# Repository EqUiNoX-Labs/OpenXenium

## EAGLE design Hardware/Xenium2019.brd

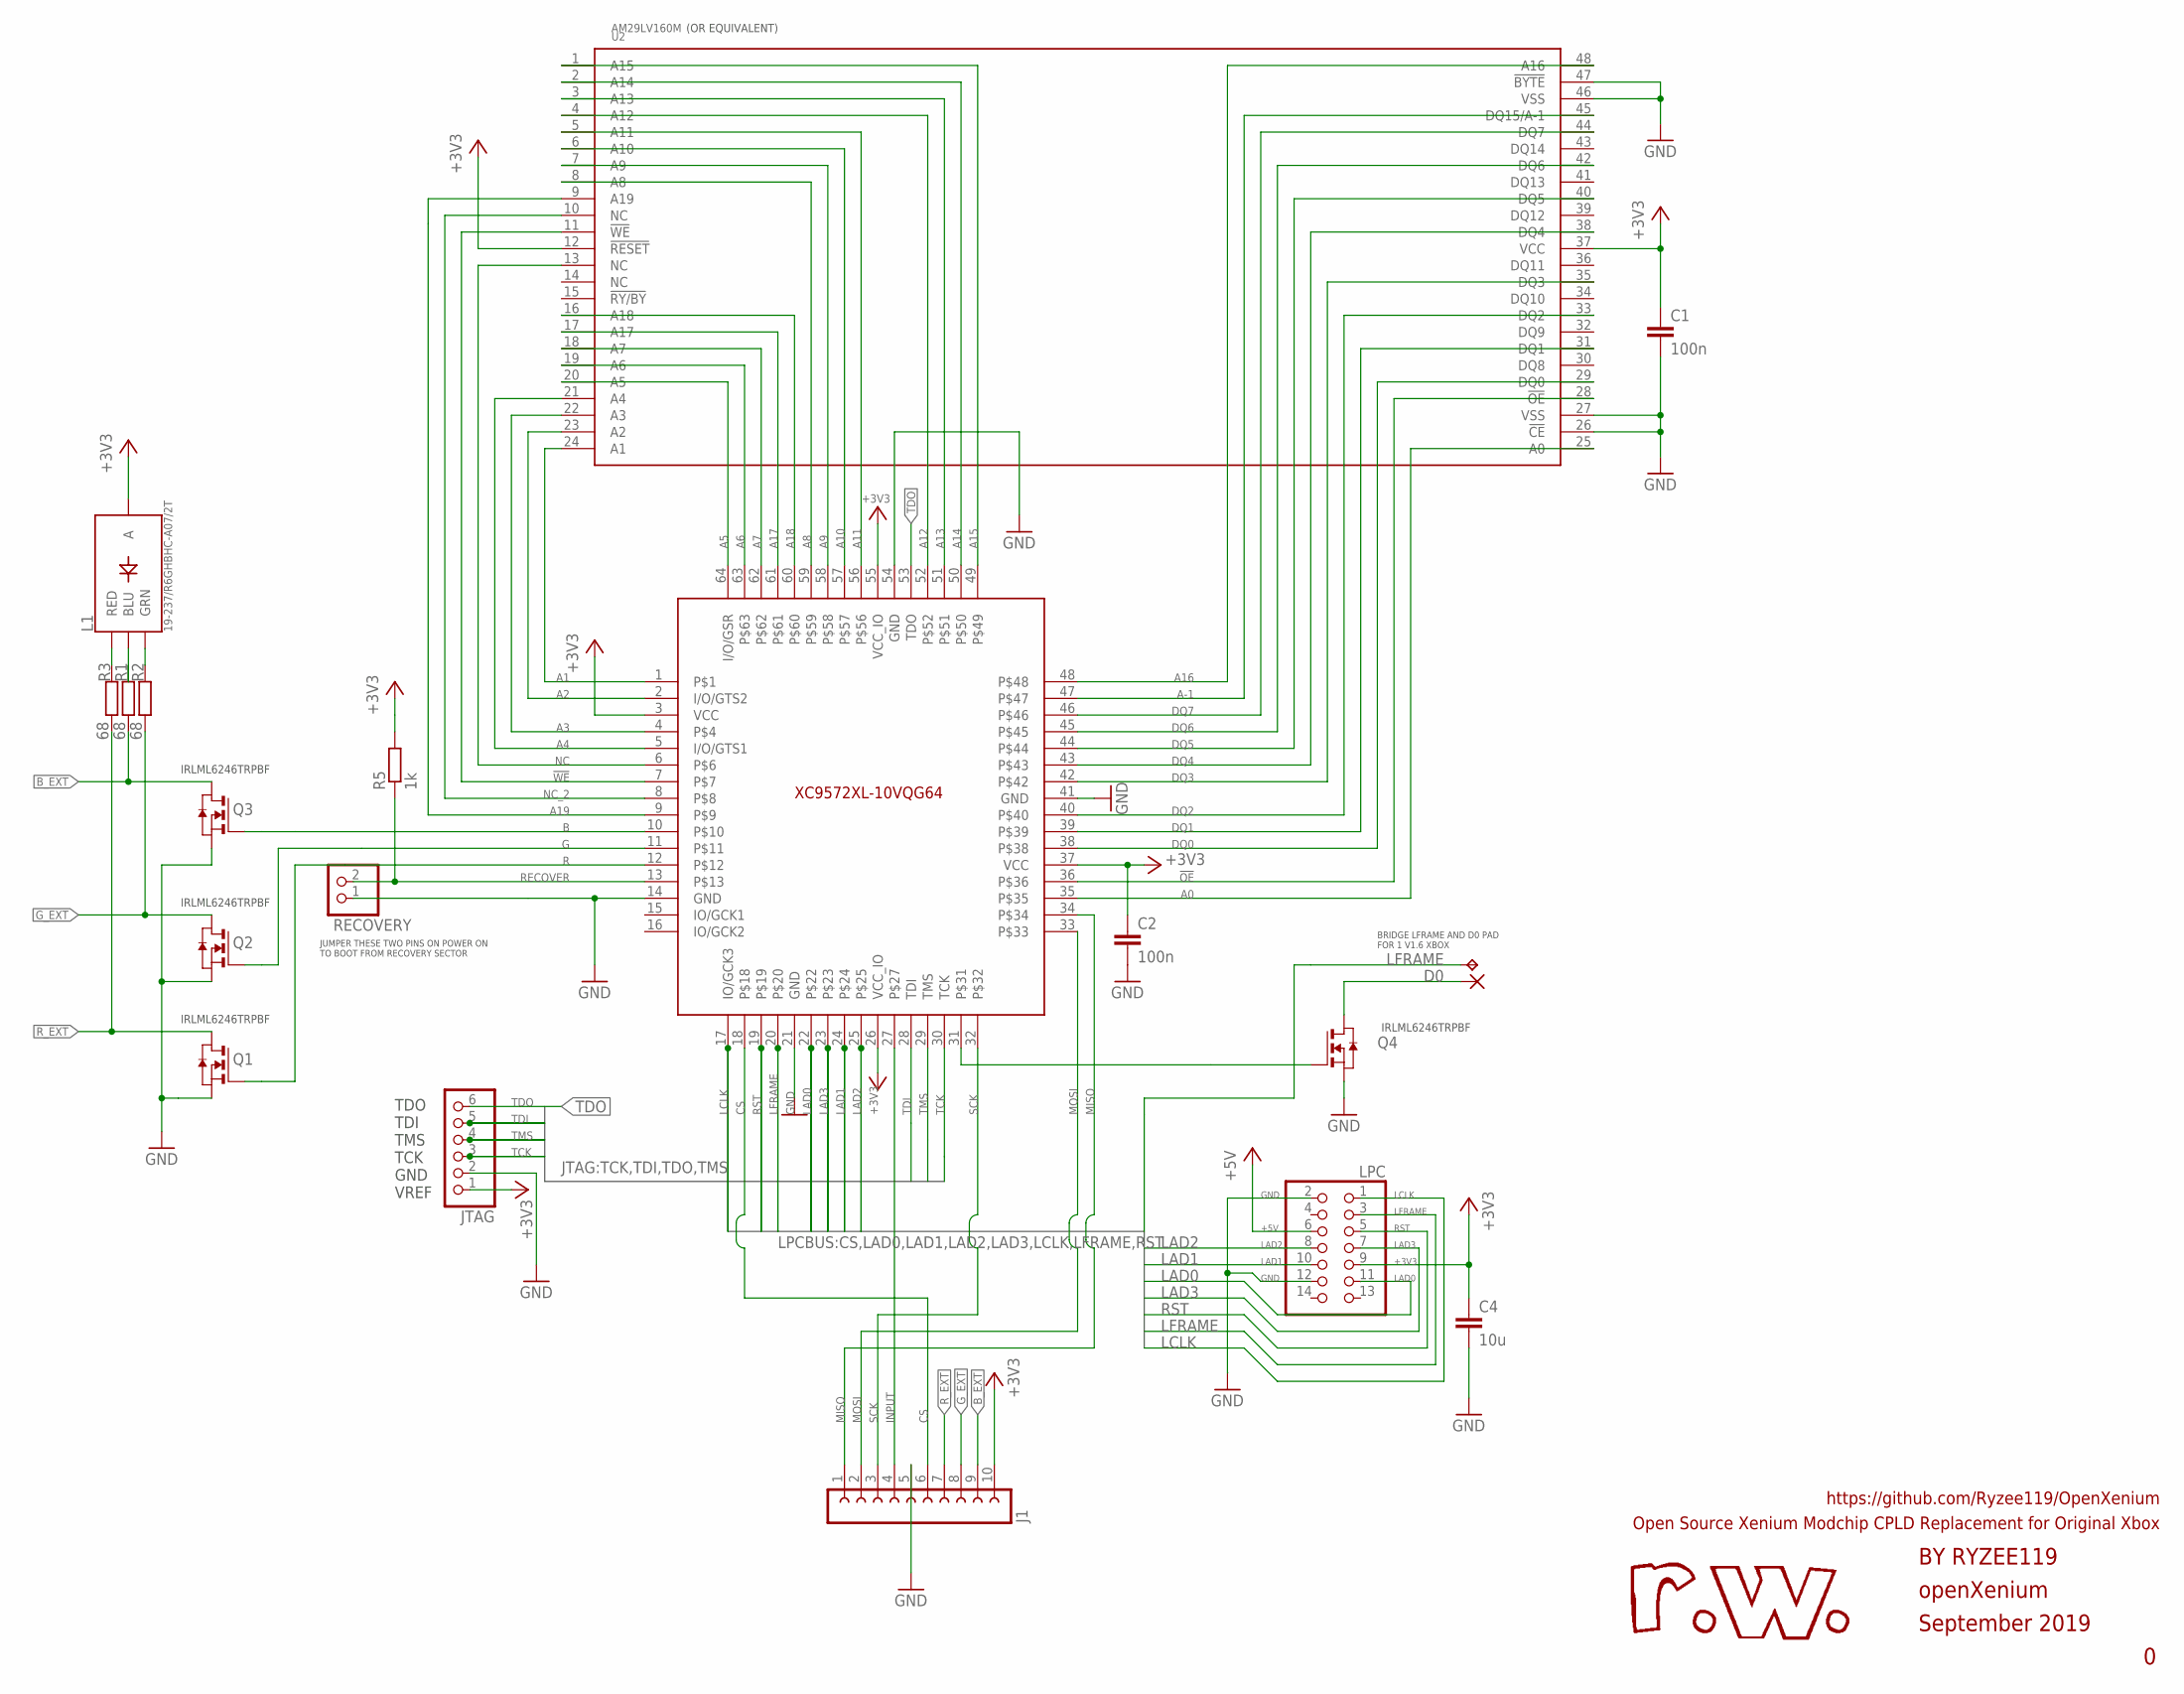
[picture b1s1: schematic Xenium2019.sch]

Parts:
C1, C2: 100n; C0603
C4: 10u; C0603
D0: SMD2; SMD1,27-2,54
J1: FE10-1; FE10
JTAG: PINHD-1X6; 1X06
L1: 19-237/R6GHBHC-A07/2T; 4-SMD-R6GHBHC
LPC: PINHD-2X7; 2X07
Q1, Q2, Q3, Q4: 310mA/60V/1.6Ω; SOT-23
R1, R2, R3: 68; R0603
R5: 1k; R0603
RECOVERY: PINHD-1X2; 1X02
TP1: TPTP13SQ; TP13SQ
U1: XC9572XL-10VQG64; LQFP64
U2: AM29LV160M; TSOP48

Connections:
!OE: U1.36, U2.28 (!OE)
!WE: U1.7, U2.11 (!WE)
+3V3: C1.1, C2.1, C4.1, J1.10, JTAG.1, L1.P$2 (A), LPC.9, R5.2, U1.3 (VCC), U1.26 (VCC_IO), U1.37 (VCC), U1.55 (VCC_IO), U2.12 (!RESET), U2.37 (VCC)
+5V: LPC.6
A0: U1.35, U2.25 (A0)
A1: U1.1, U2.24 (A1)
A2: U1.2 (I/O/GTS2), U2.23 (A2)
A3: U1.4, U2.22 (A3)
A4: U1.5 (I/O/GTS1), U2.21 (A4)
A5: U1.64 (I/O/GSR), U2.20 (A5)
A6: U1.63, U2.19 (A6)
A7: U1.62, U2.18 (A7)
A8: U1.59, U2.8 (A8)
A9: U1.58, U2.7 (A9)
A10: U1.57, U2.6 (A10)
A11: U1.56, U2.5 (A11)
A12: U1.52, U2.4 (A12)
A13: U1.51, U2.3 (A13)
A14: U1.50, U2.2 (A14)
A15: U1.49, U2.1 (A15)
A16: U1.48, U2.48 (A16)
A17: U1.61, U2.17 (A17)
A18: U1.60, U2.16 (A18)
A19: U1.9, U2.9 (A19)
A-1: U1.47, U2.45 (DQ15/A-1)
B: Q3.3 (G), U1.10
BLUE: L1.P$4 (BLU), R1.1
B_EXT: J1.9, Q3.1 (D), R1.2
CS: J1.6, U1.18
DQ0: U1.38, U2.29 (DQ0)
DQ1: U1.39, U2.31 (DQ1)
DQ2: U1.40, U2.33 (DQ2)
DQ3: U1.42, U2.35 (DQ3)
DQ4: U1.43, U2.38 (DQ4)
DQ5: U1.44, U2.40 (DQ5)
DQ6: U1.45, U2.42 (DQ6)
DQ7: U1.46, U2.44 (DQ7)
G: Q2.3 (G), U1.11
GND: C1.2, C2.2, C4.2, J1.5, JTAG.2, LPC.2, LPC.12, Q1.2 (S), Q2.2 (S), Q3.2 (S), Q4.2 (S), RECOVERY.1, U1.14 (GND), U1.21 (GND), U1.41 (GND), U1.54 (GND), U2.26 (!CE), U2.27 (VSS), U2.46 (VSS), U2.47 (!BYTE)
GREEN: L1.P$3 (GRN), R2.1
G_EXT: J1.8, Q2.1 (D), R2.2
INPUT: J1.4, U1.27
LAD0: LPC.11, U1.22
LAD1: LPC.10, U1.24
LAD2: LPC.8, U1.25
LAD3: LPC.7, U1.23
LCLK: LPC.1, U1.17 (IO/GCK3)
LFRAME: LPC.3, TP1.TP, U1.20
MISO: J1.1, U1.34
MOSI: J1.2, U1.33
unnamed: Q4.3 (G), U1.31
unnamed: D0.1, Q4.1 (D)
NC: U1.6, U2.13 (NC)
NC_2: U1.8, U2.10 (NC)
R: Q1.3 (G), U1.12
RECOVER: R5.1, RECOVERY.2, U1.13
RED: L1.P$1 (RED), R3.1
RST: LPC.5, U1.19
R_EXT: J1.7, Q1.1 (D), R3.2
SCK: J1.3, U1.32
TCK: JTAG.3, U1.30 (TCK)
TDI: JTAG.5, U1.28 (TDI)
TDO: JTAG.6, U1.53 (TDO)
TMS: JTAG.4, U1.29 (TMS)

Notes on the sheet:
TDO TDI TMS TCK GND VREF
openXenium
September 2019
BY RYZEE119
Open Source Xenium Modchip CPLD Replacement for Original Xbox
https://github.com/Ryzee119/OpenXenium
BRIDGE LFRAME AND D0 PAD FOR 1 V1.6 XBOX
JUMPER THESE TWO PINS ON POWER ON TO BOOT FROM RECOVERY SECTOR
IRLML6246TRPBF
(OR EQUIVALENT)

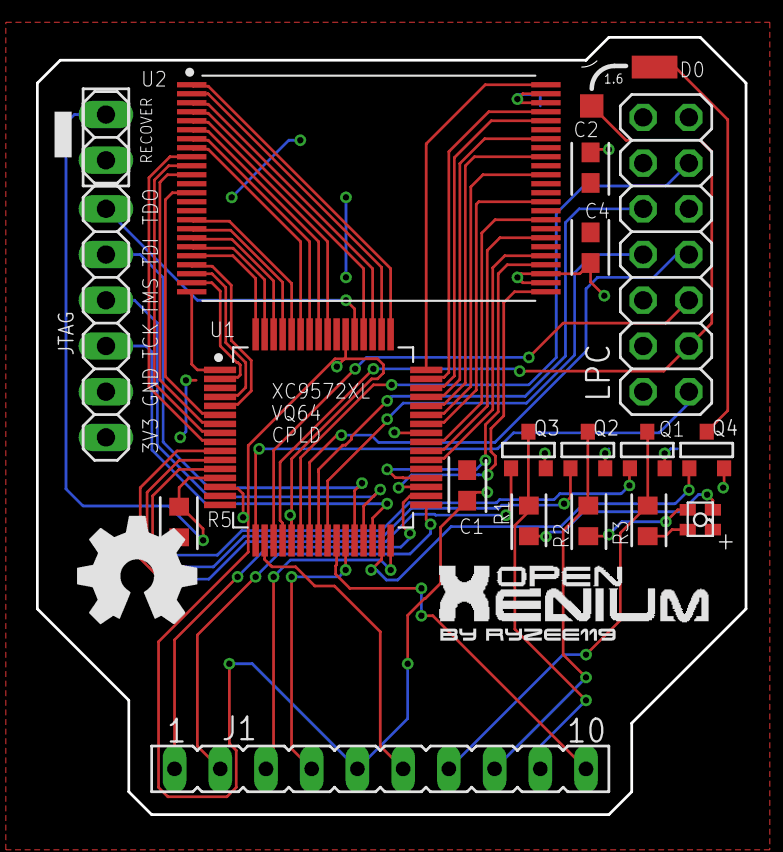
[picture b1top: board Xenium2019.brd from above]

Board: 2 copper layers, 39.4 x 43.2 mm, 20 parts (0 on the bottom side), 63 nets.

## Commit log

2021-10-10 Update: added pads
2021-10-10 Update: wired header
2025-12-05 updated logic
2025-12-06 fix register
